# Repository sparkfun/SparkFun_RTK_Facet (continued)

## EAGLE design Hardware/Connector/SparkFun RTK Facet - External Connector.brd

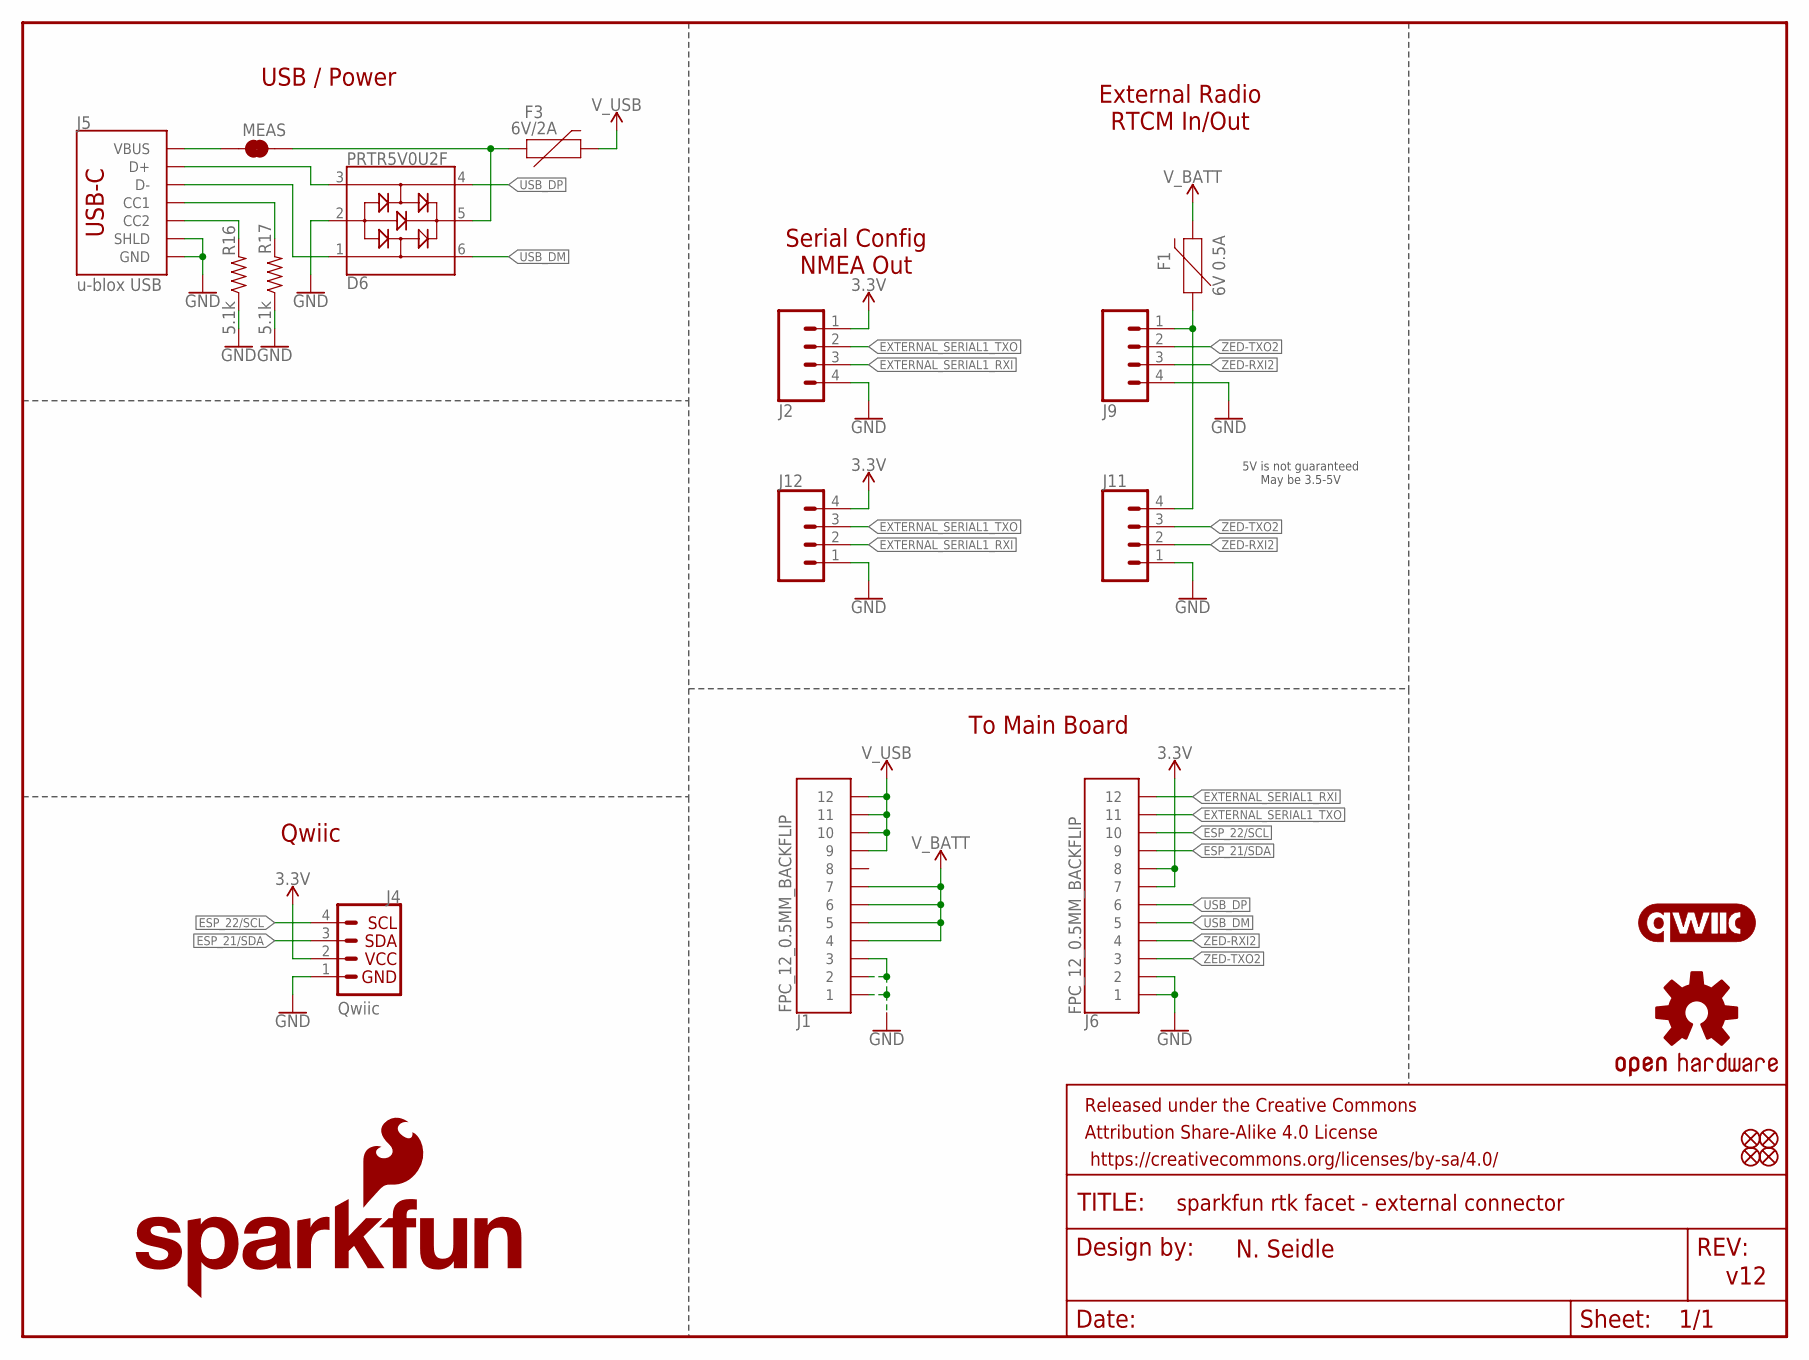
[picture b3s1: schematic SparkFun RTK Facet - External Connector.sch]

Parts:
D6: PRTR5V0U2F; SOT886
F1: 6V 0.5A; 0805
F3: 6V/2A; 1210
FRAME1: FRAME-LETTER; CREATIVE_COMMONS
J1, J6: FPC_12_0.5MM_BACKFLIP; FPC_12_DOUBLESIDED_BACKFLIP
J2, J9: CONN_04JST-SMD-LOCKING; JST-4-SMD-1.25MM-LOCKING
J4: Qwiic; JST04_1MM_RA
J5: u-blox USB; USB-C-16P-2LAYER-PADS
J11, J12: CONN_041X04_NO_SILK_NO_POP; 1X04_NO_SILK
JP21, JP61, JP71, JP81: FIDUCIALUFIDUCIAL; FIDUCIAL-MICRO
LOGO1: OSHW-LOGOMINI; OSHW-LOGO-MINI
LOGO2: SFE_LOGO_NAME_FLAME.1_INCH; SFE_LOGO_NAME_FLAME_.1
LOGO3: QWIIC_LOGO_CONNECTOR; QWIIC_5.5MM
MEAS: JUMPER-COMBO_2_NC_TRACE; COMBO-JUMPER_2_NC_TRACE
R16, R17: 5.1k; 0603

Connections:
3.3V: J2.1, J4.2, J6.7, J6.8, J12.4
CC1: J5.A5 (CC1), R17.2
CC2: J5.B5 (CC2), R16.2
ESP_21/SDA: J4.3, J6.9
ESP_22/SCL: J4.4, J6.10
EXTERNAL_SERIAL1_RXI: J2.3, J6.12, J12.2
EXTERNAL_SERIAL1_TXO: J2.2, J6.11, J12.3
GND: D6.2, J1.1, J1.2, J1.3, J2.4, J4.1, J5.GND, J5.GND2 (GND), J5.SHLD1 (SHLD), J5.SHLD2 (SHLD), J5.SHLD3 (SHLD), J5.SHLD4 (SHLD), J6.1, J6.2, J9.4, J11.1, J12.1, R16.1, R17.1
unnamed: F1.1, J9.1, J11.4
USB1_D_M: D6.1, J5.A7 (D-), J5.B7 (D-)
USB1_D_P: D6.3, J5.A6 (D+), J5.B6 (D+)
USB_DM: D6.6, J6.5
USB_DP: D6.4, J6.6
VIN: J5.VBUS1 (VBUS), J5.VBUS2 (VBUS), MEAS.1, MEAS.3 (1)
VIN1: D6.5, F3.1, MEAS.2, MEAS.4 (2)
V_BATT: F1.2, J1.4, J1.5, J1.6, J1.7
V_USB: F3.2, J1.9, J1.10, J1.11, J1.12
ZED-RXI2: J6.4, J9.3, J11.2
ZED-TXO2: J6.3, J9.2, J11.3

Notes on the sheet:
v12
USB / Power
External Radio RTCM In/Out
Serial Config NMEA Out
5V is not guaranteed May be 3.5-5V
To Main Board
Qwiic
N. Seidle

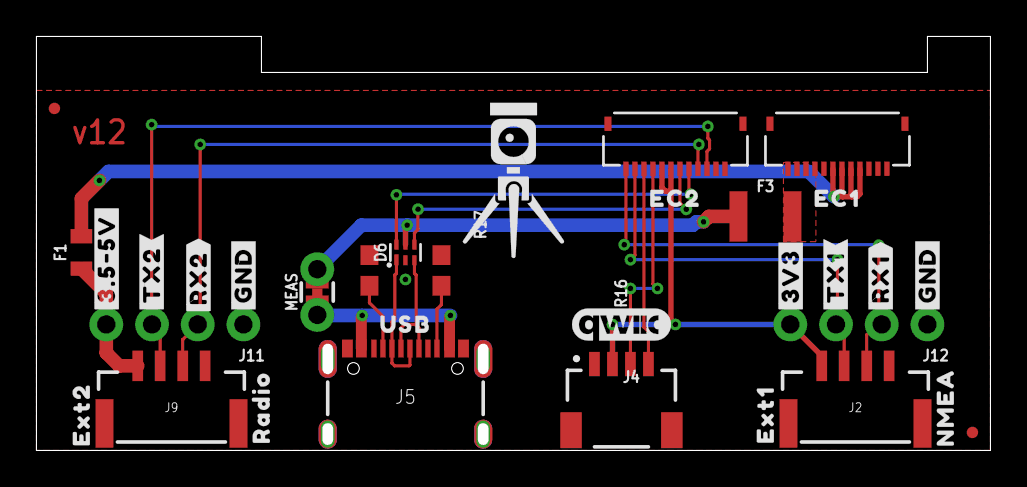
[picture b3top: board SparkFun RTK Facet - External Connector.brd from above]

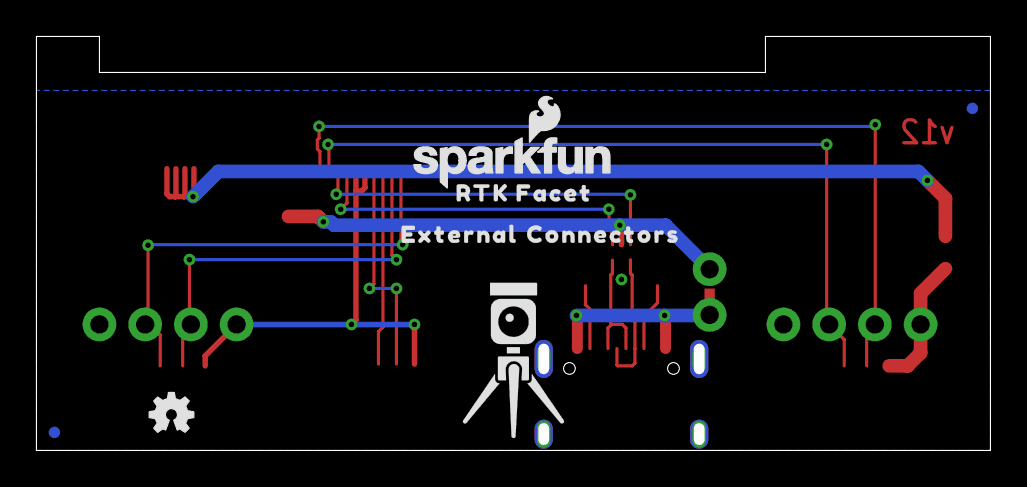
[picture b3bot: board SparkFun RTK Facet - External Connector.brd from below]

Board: 2 copper layers, 53.0 x 23.0 mm, 42 parts (8 on the bottom side), 19 nets.

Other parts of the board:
U$1: USB0
U$2: CONNECTORS1
U$3, U$13: RTK5#SVG0
U$4: EXT10
U$5: #3V3#0
U$6: EXT22
U$7: NMEA1
U$8: EC10
U$9: EXTERNAL0
U$11: EC21
U$12: RADIO3
U$14: RTK_FACET0
U$23: #3#5#5V#0
U$38, U$82: #GND#0
U$39: #RX2#2
U$40: #TX2#1
U$65: #TX1#1
U$68: #RX1#2

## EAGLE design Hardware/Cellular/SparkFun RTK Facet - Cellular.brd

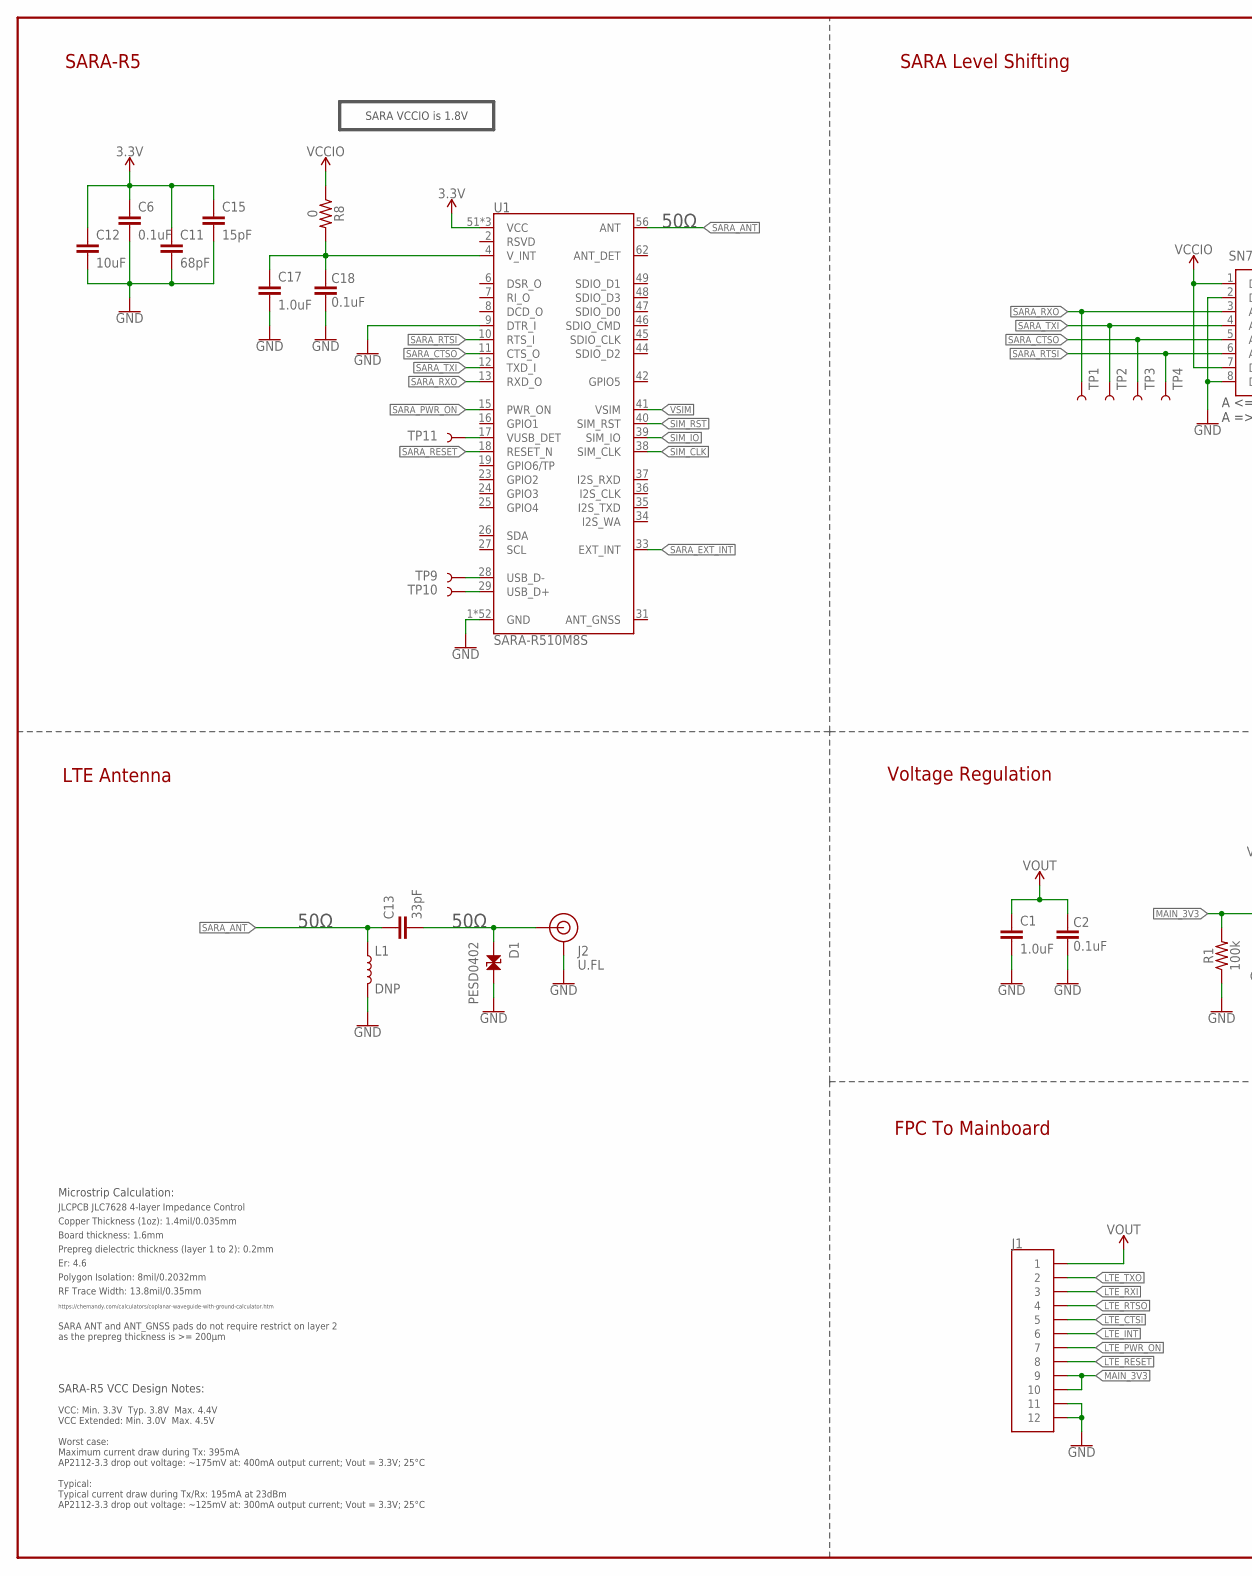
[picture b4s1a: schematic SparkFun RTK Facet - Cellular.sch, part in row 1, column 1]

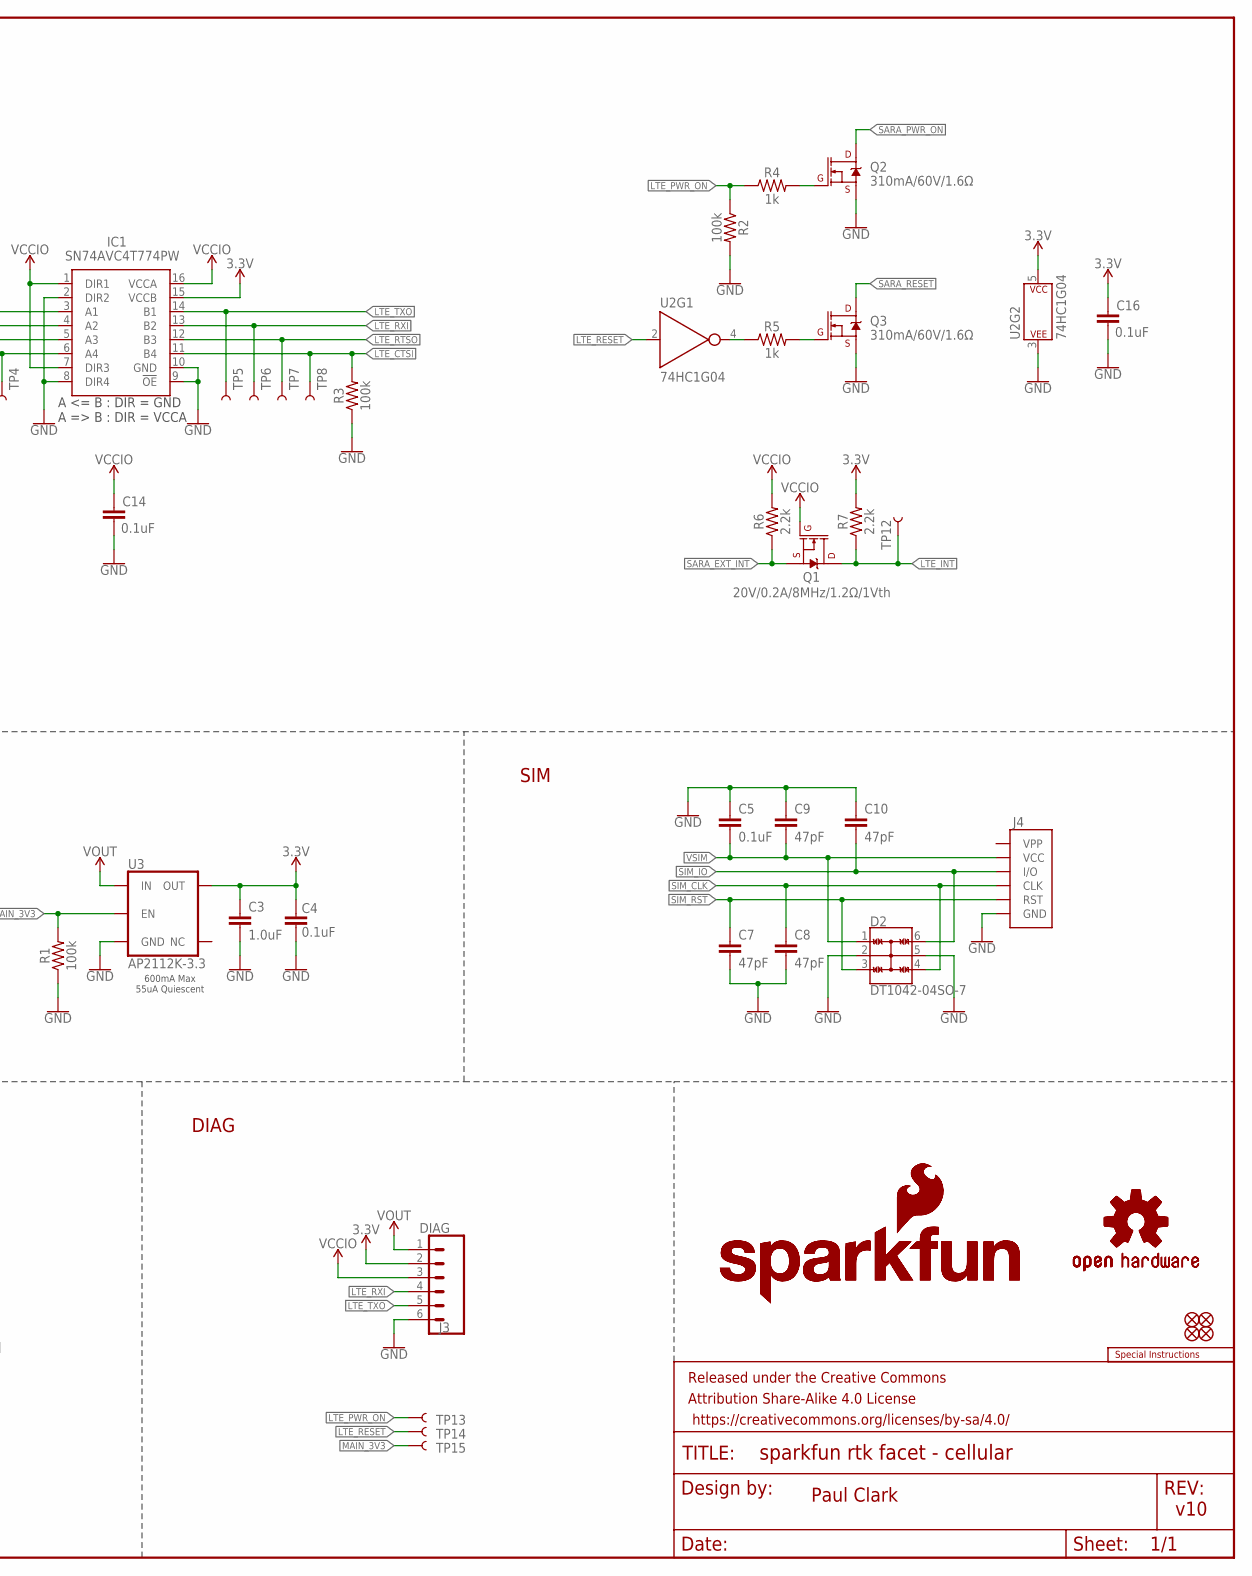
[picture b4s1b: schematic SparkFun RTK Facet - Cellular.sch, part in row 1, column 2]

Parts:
C1, C3, C17: 1.0uF; 0603
C2, C4, C5, C6, C14, C16, C18: 0.1uF; 0603
C7, C8, C9, C10: 47pF; 0603
C11: 68pF; 0603
C12: 10uF; 0603
C13: 33pF; 0402
C15: 15pF; 0603
D1: PESD0402; 0402
D2: DT1042-04SO-7; SOT23-6L
FID1, FID2, FID3, FID4: FIDUCIAL1X2; FIDUCIAL-1X2
FRAME3: FRAME-LEDGER; CREATIVE_COMMONS
IC1: SN74AVC4T774PW; SOP65P640X120-16N
J1: FPC_12_0.5MM_BACKFLIP; FPC_12_DOUBLESIDED_BACKFLIP
J2: U.FL
J3: DIAG; 1X06_NO_SILK
J4: SIMHOLDER-PUSHPUSH-REDUCED-PADS; NANO_SIM_PP_REDUCED_PADS
L1: DNP; 0402_COILCRAFT
LOGO1: SPECIAL_INSTRUCTIONS-ORDERING; ORDERING_INSTRUCTIONS
LOGO2, LOGO5: SFE_LOGO_NAME_FLAME.1_INCH; SFE_LOGO_NAME_FLAME_.1
LOGO3, LOGO4: OSHW-LOGOMINI; OSHW-LOGO-MINI
Q1: 20V/0.2A/8MHz/1.2Ω/1Vth; SOT-416FL
Q2, Q3: 310mA/60V/1.6Ω; SOT323
R1, R2, R3: 100k; 0603
R4, R5: 1k; 0603
R6, R7: 2.2k; 0603
R8: 0; 0603
TP1, TP2, TP3, TP4, TP5, TP6, TP7, TP8, TP9, TP10, TP11, TP12, TP13, TP14, TP15: TEST-POINT3; PAD.03X.03
U1: SARA-R510M8S; SARA-LGA
U2: 74HC1G04; SOT353
U3: AP2112K-3.3; SOT23-5

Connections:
3.3V: C3.1, C4.2, C6.1, C11.1, C12.1, C15.1, C16.1, IC1.15 (VCCB), J3.2, R7.2, U1.51 (VCC), U1.52 (VCC), U1.53 (VCC), U2.5 (P$V+), U3.5 (OUT)
GND: C1.2, C2.1, C3.2, C4.1, C5.1, C6.2, C7.2, C8.2, C9.1, C10.1, C11.2, C12.2, C14.2, C15.2, C16.2, C17.2, C18.1, D1.2, D2.2, D2.5, IC1.2 (DIR2), IC1.8 (DIR4), IC1.9 (!OE), IC1.10 (GND), J1.11, J1.12, J2.1 (GND), J2.2 (GND), J3.6, J4.C5 (GND), L1.P$2 (2), Q2.2 (S), Q3.2 (S), R1.1, R2.2, R3.1, U1.1 (GND), U1.3 (GND), U1.5 (GND), U1.9 (DTR_I), U1.14 (GND), U1.20 (GND), U1.21 (GND), U1.22 (GND), U1.30 (GND), U1.32 (GND), U1.43 (GND), U1.50 (GND), U1.54 (GND), U1.55 (GND), U1.57 (GND), U1.58 (GND), U1.59 (GND), U1.60 (GND), U1.61 (GND), U1.63 (GND), U1.64 (GND), U1.65 (GND), U1.66 (GND), U1.67 (GND), U1.68 (GND), U1.69 (GND), U1.70 (GND), U1.71 (GND), U1.72 (GND), U1.73 (GND), U1.74 (GND), U1.75 (GND), U1.76 (GND), U1.77 (GND), U1.78 (GND), U1.79 (GND), U1.80 (GND), U1.81 (GND), U1.82 (GND), U1.83 (GND), U1.84 (GND), U1.85 (GND), U1.86 (GND), U1.87 (GND), U1.88 (GND), U1.89 (GND), U1.90 (GND), U1.91 (GND), U1.92 (GND), U1.93 (GND), U1.94 (GND), U1.95 (GND), U1.96 (GND), U2.3 (P$V-), U3.2 (GND)
LTE_!RESET!: J1.8, TP14.1, U2.2 (A)
LTE_CTSI: IC1.11 (B4), J1.5, R3.2, TP8.1
LTE_INT: J1.6, Q1.3 (D), R7.1, TP12.1
LTE_PWR_ON: J1.7, R2.1, R4.1, TP13.1
LTE_RTSO: IC1.12 (B3), J1.4, TP7.1
LTE_RXI: IC1.13 (B2), J1.3, J3.4, TP6.1
LTE_TXO: IC1.14 (B1), J1.2, J3.5, TP5.1
MAIN_3V3: J1.9, J1.10, R1.2, TP15.1, U3.3 (EN)
unnamed: TP9.1, U1.28 (USB_D-)
unnamed: TP10.1, U1.29 (USB_D+)
unnamed: TP11.1, U1.17 (VUSB_DET)
unnamed: C13.2, D1.1, J2.FEED (SIGNAL)
unnamed: Q2.1 (G), R4.2
unnamed: Q3.1 (G), R5.2
unnamed: R5.1, U2.4 (Y)
unnamed: C17.1, C18.2, R8.2, U1.4 (V_INT)
SARA_!RESET!: Q3.3 (D), U1.18 (RESET_N)
SARA_ANT: C13.1, L1.P$1 (1), U1.56 (ANT)
SARA_CTSO: IC1.5 (A3), TP3.1, U1.11 (CTS_O)
SARA_EXT_INT: Q1.2 (S), R6.1, U1.33 (EXT_INT)
SARA_PWR_ON: Q2.3 (D), U1.15 (PWR_ON)
SARA_RTSI: IC1.6 (A4), TP4.1, U1.10 (RTS_I)
SARA_RXO: IC1.3 (A1), TP1.1, U1.13 (RXD_O)
SARA_TXI: IC1.4 (A2), TP2.1, U1.12 (TXD_I)
SIM_CLK: C8.1, D2.4, J4.C3 (CLK), U1.38 (SIM_CLK)
SIM_IO: C10.2, D2.6, J4.C7 (I/O), U1.39 (SIM_IO)
SIM_RST: C7.1, D2.3, J4.C2 (RST), U1.40 (SIM_RST)
VCCIO: C14.1, IC1.1 (DIR1), IC1.7 (DIR3), IC1.16 (VCCA), J3.3, Q1.1 (G), R6.2, R8.1
VOUT: C1.1, C2.2, J1.1, J3.1, U3.1 (IN)
VSIM: C5.2, C9.2, D2.1, J4.C1 (VCC), U1.41 (VSIM)

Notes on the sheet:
v10
FPC To Mainboard
SARA-R5
50Ω
SARA VCCIO is 1.8V
SIM
DIAG
LTE Antenna
Board thickness: 1.6mm
Er: 4.6
Copper Thickness (1oz): 1.4mil/0.035mm
RF Trace Width: 13.8mil/0.35mm
Polygon Isolation: 8mil/0.2032mm
Prepreg dielectric thickness (layer 1 to 2): 0.2mm
https://chemandy.com/calculators/coplanar-waveguide-with-ground-calculator.htm
Microstrip Calculation:
SARA ANT and ANT_GNSS pads do not require restrict on layer 2 as the prepreg thickness is >= 200µm
SARA Level Shifting
SARA-R5 VCC Design Notes:
VCC: Min. 3.3V Typ. 3.8V Max. 4.4V VCC Extended: Min. 3.0V Max. 4.5V Worst case: Maximum current draw during Tx: 395mA AP2112-3.3 drop out voltage: ~175mV at: 400mA output current; Vout = 3.3V; 25°C Typical: Typical current draw during Tx/Rx: 195mA at 23dBm AP2112-3.3 drop out voltage: ~125mV at: 3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
Voltage Regulation
600mA Max 55uA Quiescent
JLCPCB JLC7628 4-layer Impedance Control
Paul Clark

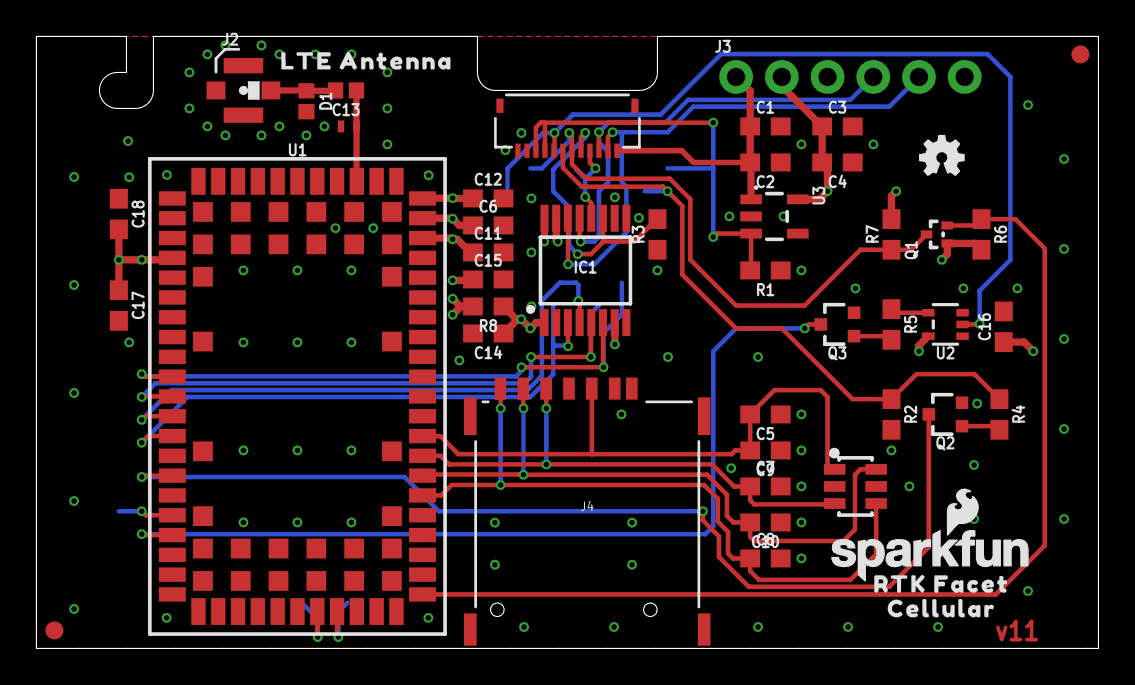
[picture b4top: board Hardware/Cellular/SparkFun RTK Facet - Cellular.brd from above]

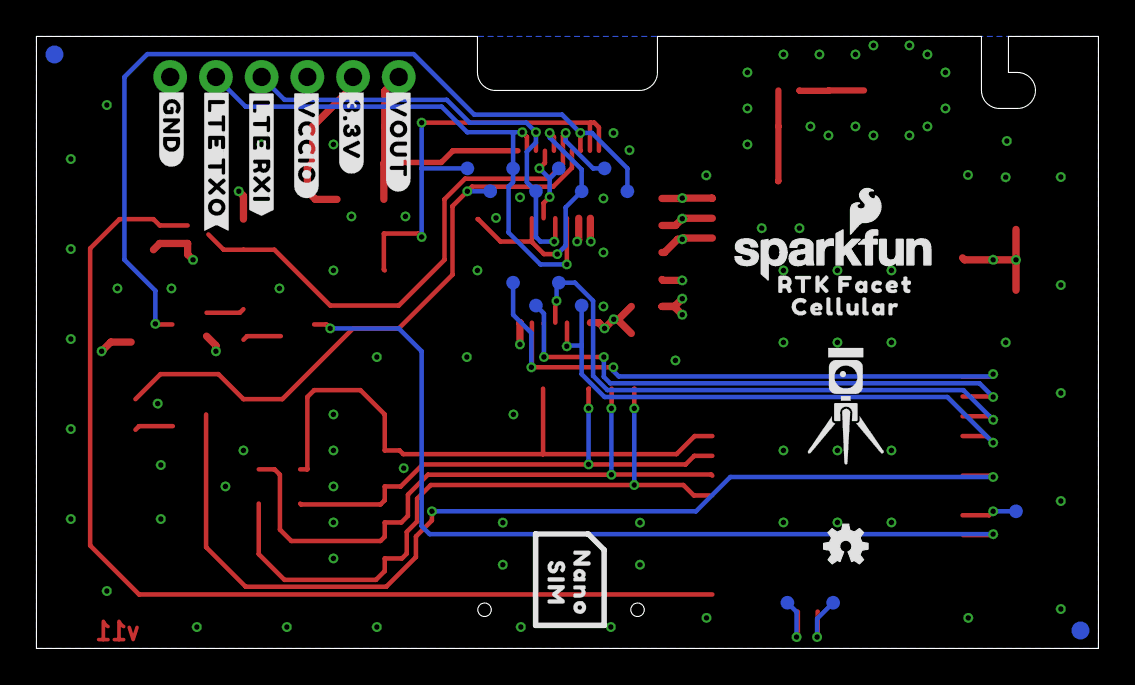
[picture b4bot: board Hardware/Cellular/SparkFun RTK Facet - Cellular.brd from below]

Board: 4 copper layers, 59.0 x 34.0 mm, 79 parts (30 on the bottom side), 32 nets.

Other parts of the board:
U$1, U$14: RTK_FACET0
U$2, U$3: CELLULAR1
U$4: #VOUT#0
U$5: #3#3V#0
U$6: #VCCIO#0
U$7: #LTE_RXI#0
U$8: #LTE_TXO#0
U$9: #GND#0
U$10: LTE_ANTENNA0
U$15: RTK5#SVG0
U$130: NANO0
U$131: SIM0

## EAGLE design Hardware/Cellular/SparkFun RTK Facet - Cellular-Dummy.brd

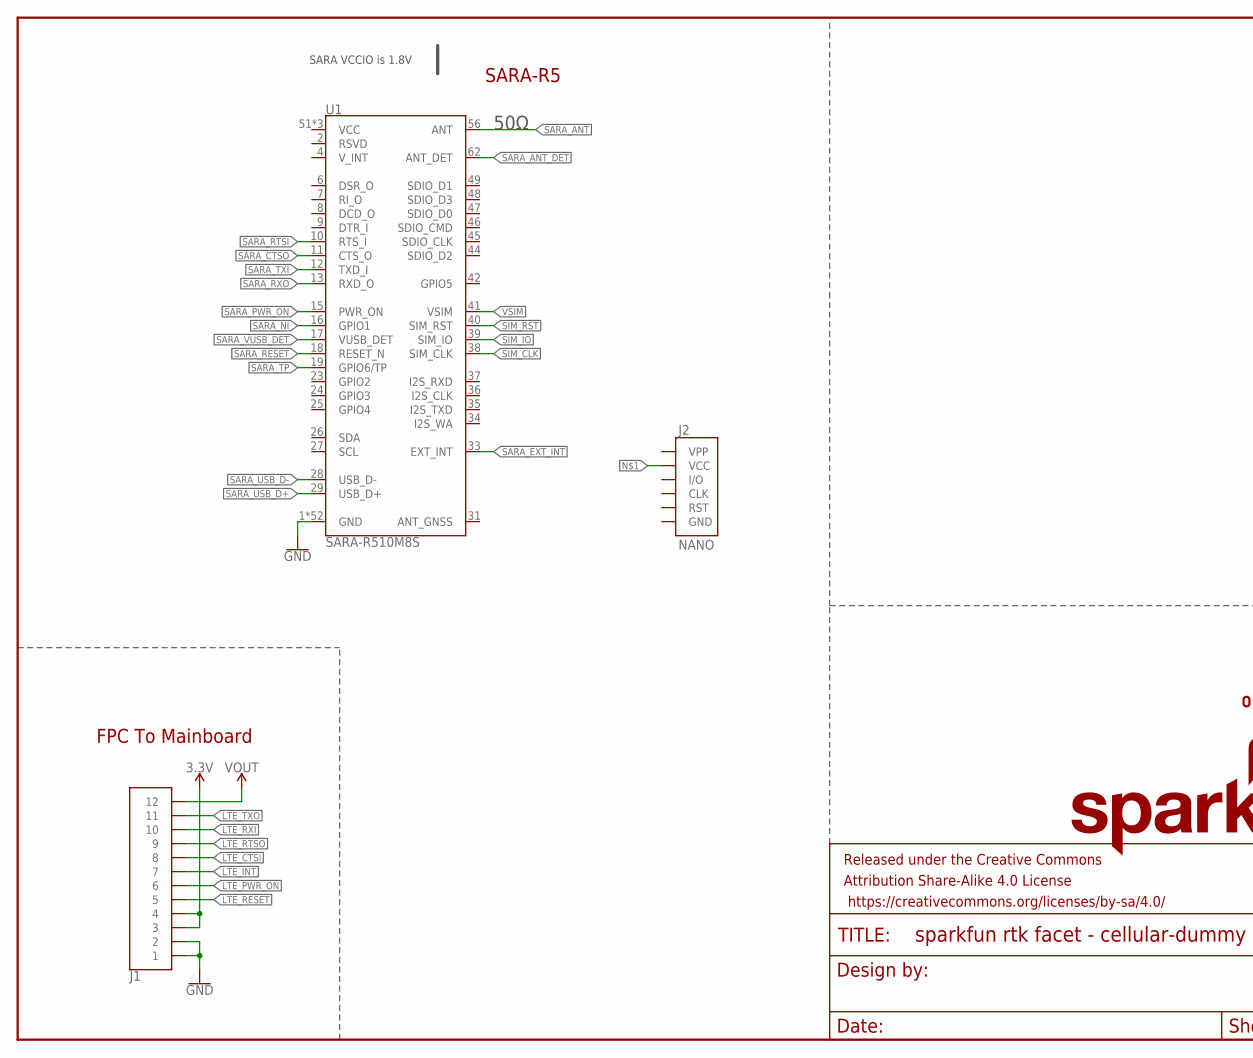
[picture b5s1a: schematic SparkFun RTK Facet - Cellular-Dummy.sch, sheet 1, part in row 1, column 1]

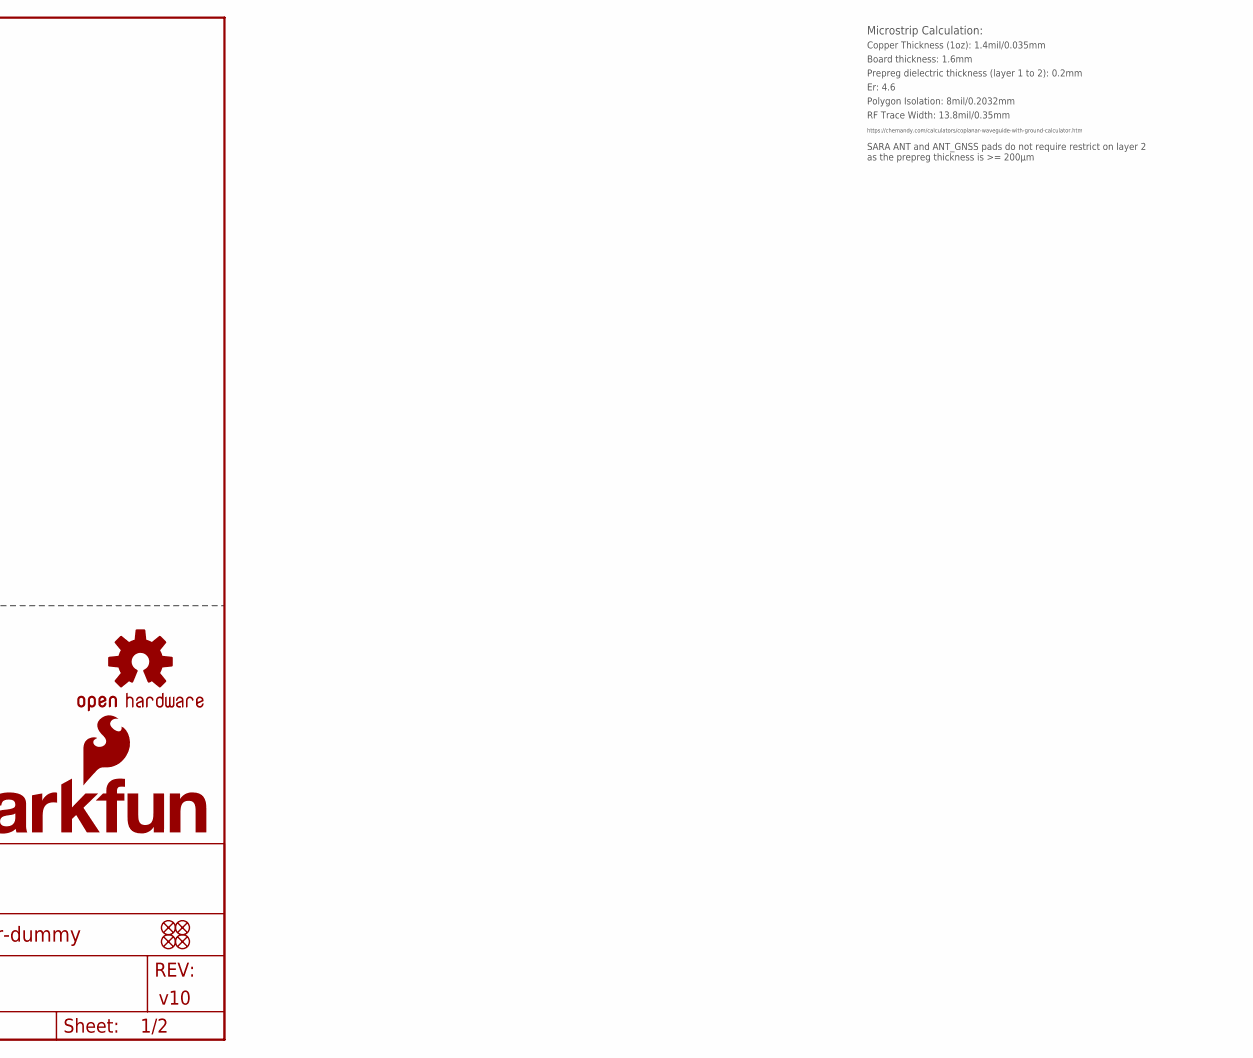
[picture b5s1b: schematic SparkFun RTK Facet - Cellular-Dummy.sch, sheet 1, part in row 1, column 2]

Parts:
FID1, FID2, FID3, FID4: FIDUCIAL1X2; FIDUCIAL-1X2
FRAME1: FRAME-LETTER; CREATIVE_COMMONS
J1: FPC_12_0.5MM_BACKFLIP; FPC_12_DOUBLESIDED_BACKFLIP
J2: NANO; NANO_SIM_PP
LOGO3: OSHW-LOGOMINI; OSHW-LOGO-MINI
LOGO5: SFE_LOGO_NAME_FLAME.1_INCH; SFE_LOGO_NAME_FLAME_.1
U1: SARA-R510M8S; SARA-LGA

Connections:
3.3V: J1.3, J1.4
GND: J1.1, J1.2, J2.C5 (GND), U1.1 (GND), U1.3 (GND), U1.5 (GND), U1.14 (GND), U1.20 (GND), U1.21 (GND), U1.22 (GND), U1.30 (GND), U1.32 (GND), U1.43 (GND), U1.50 (GND), U1.54 (GND), U1.55 (GND), U1.57 (GND), U1.58 (GND), U1.59 (GND), U1.60 (GND), U1.61 (GND), U1.63 (GND), U1.64 (GND), U1.65 (GND), U1.66 (GND), U1.67 (GND), U1.68 (GND), U1.69 (GND), U1.70 (GND), U1.71 (GND), U1.72 (GND), U1.73 (GND), U1.74 (GND), U1.75 (GND), U1.76 (GND), U1.77 (GND), U1.78 (GND), U1.79 (GND), U1.80 (GND), U1.81 (GND), U1.82 (GND), U1.83 (GND), U1.84 (GND), U1.85 (GND), U1.86 (GND), U1.87 (GND), U1.88 (GND), U1.89 (GND), U1.90 (GND), U1.91 (GND), U1.92 (GND), U1.93 (GND), U1.94 (GND), U1.95 (GND), U1.96 (GND)
LTE_!RESET!: J1.5
LTE_CTSI: J1.8
LTE_INT: J1.7
LTE_PWR_ON: J1.6
LTE_RTSO: J1.9
LTE_RXI: J1.10
LTE_TXO: J1.11
SARA_!RESET!: U1.18 (RESET_N)
SARA_ANT: U1.56 (ANT)
SARA_ANT_DET: U1.62 (ANT_DET)
SARA_CTSO: U1.11 (CTS_O)
SARA_EXT_INT: U1.33 (EXT_INT)
SARA_NI: U1.16 (GPIO1)
SARA_PWR_ON: U1.15 (PWR_ON)
SARA_RTSI: U1.10 (RTS_I)
SARA_RXO: U1.13 (RXD_O)
SARA_TP: U1.19 (GPIO6/TP)
SARA_TXI: U1.12 (TXD_I)
SARA_USB_D+: U1.29 (USB_D+)
SARA_USB_D-: U1.28 (USB_D-)
SARA_VUSB_DET: U1.17 (VUSB_DET)
SIM_CLK: U1.38 (SIM_CLK)
SIM_IO: U1.39 (SIM_IO)
SIM_RST: U1.40 (SIM_RST)
VCC: U1.51 (VCC), U1.52 (VCC), U1.53 (VCC)
VOUT: J1.12
VSIM: U1.41 (VSIM)

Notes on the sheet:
v10
FPC To Mainboard
SARA-R5
50Ω
SARA VCCIO is 1.8V
Board thickness: 1.6mm
Er: 4.6
Copper Thickness (1oz): 1.4mil/0.035mm
RF Trace Width: 13.8mil/0.35mm
Polygon Isolation: 8mil/0.2032mm
Prepreg dielectric thickness (layer 1 to 2): 0.2mm
https://chemandy.com/calculators/coplanar-waveguide-with-ground-calculator.htm
Microstrip Calculation:
SARA ANT and ANT_GNSS pads do not require restrict on layer 2 as the prepreg thickness is >= 200µm

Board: 2 copper layers, 15 parts (9 on the bottom side), 3 nets, no tracks yet.

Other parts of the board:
U$2: CELLULAR1
U$13: CELLULAR0
U$14: RTK_FACET0
U$130: NANO0
U$131: SIM0

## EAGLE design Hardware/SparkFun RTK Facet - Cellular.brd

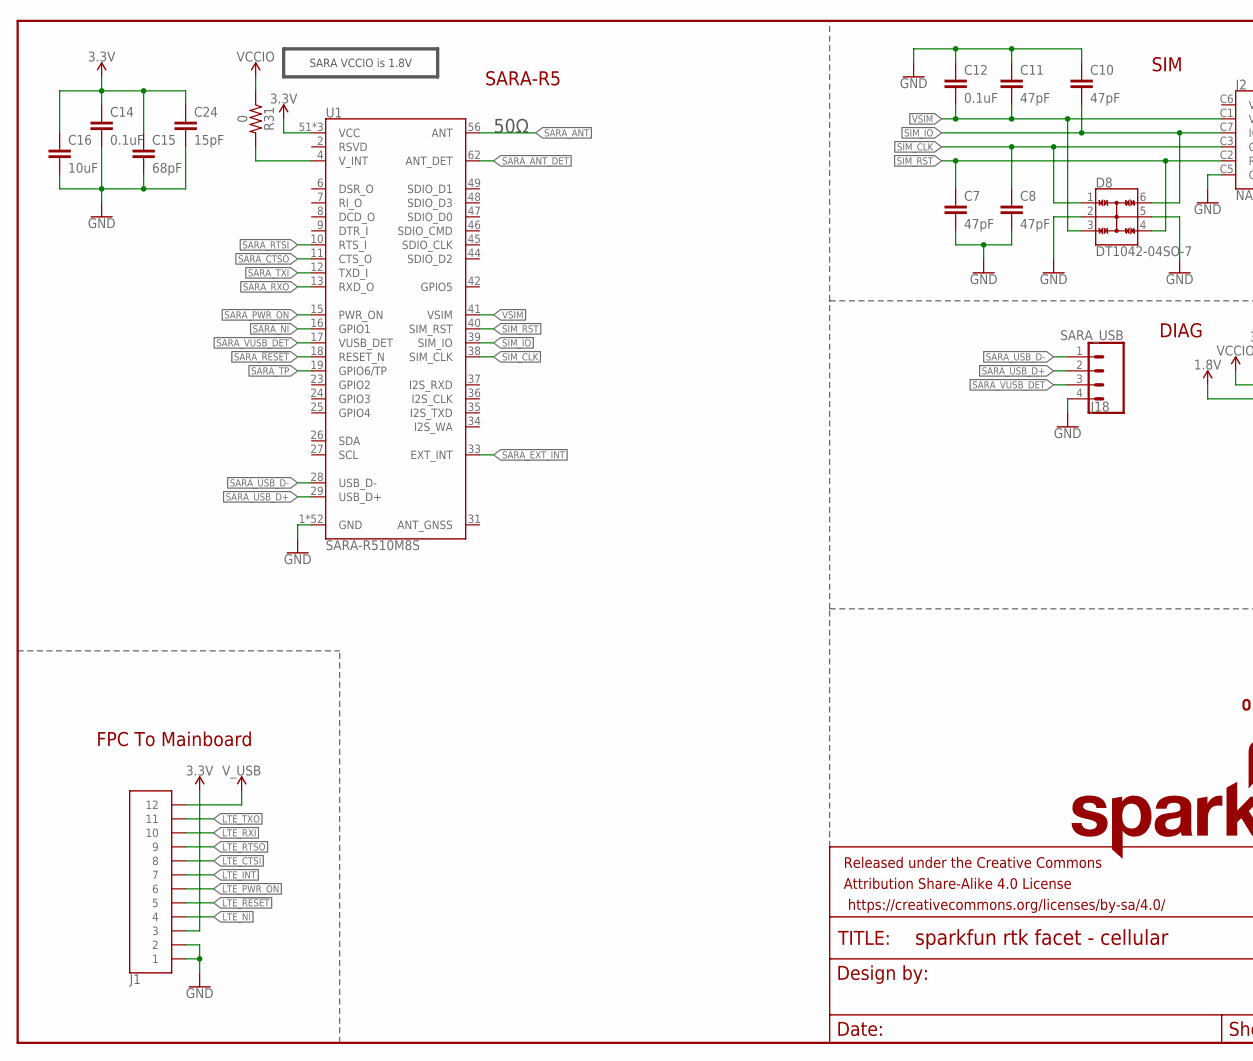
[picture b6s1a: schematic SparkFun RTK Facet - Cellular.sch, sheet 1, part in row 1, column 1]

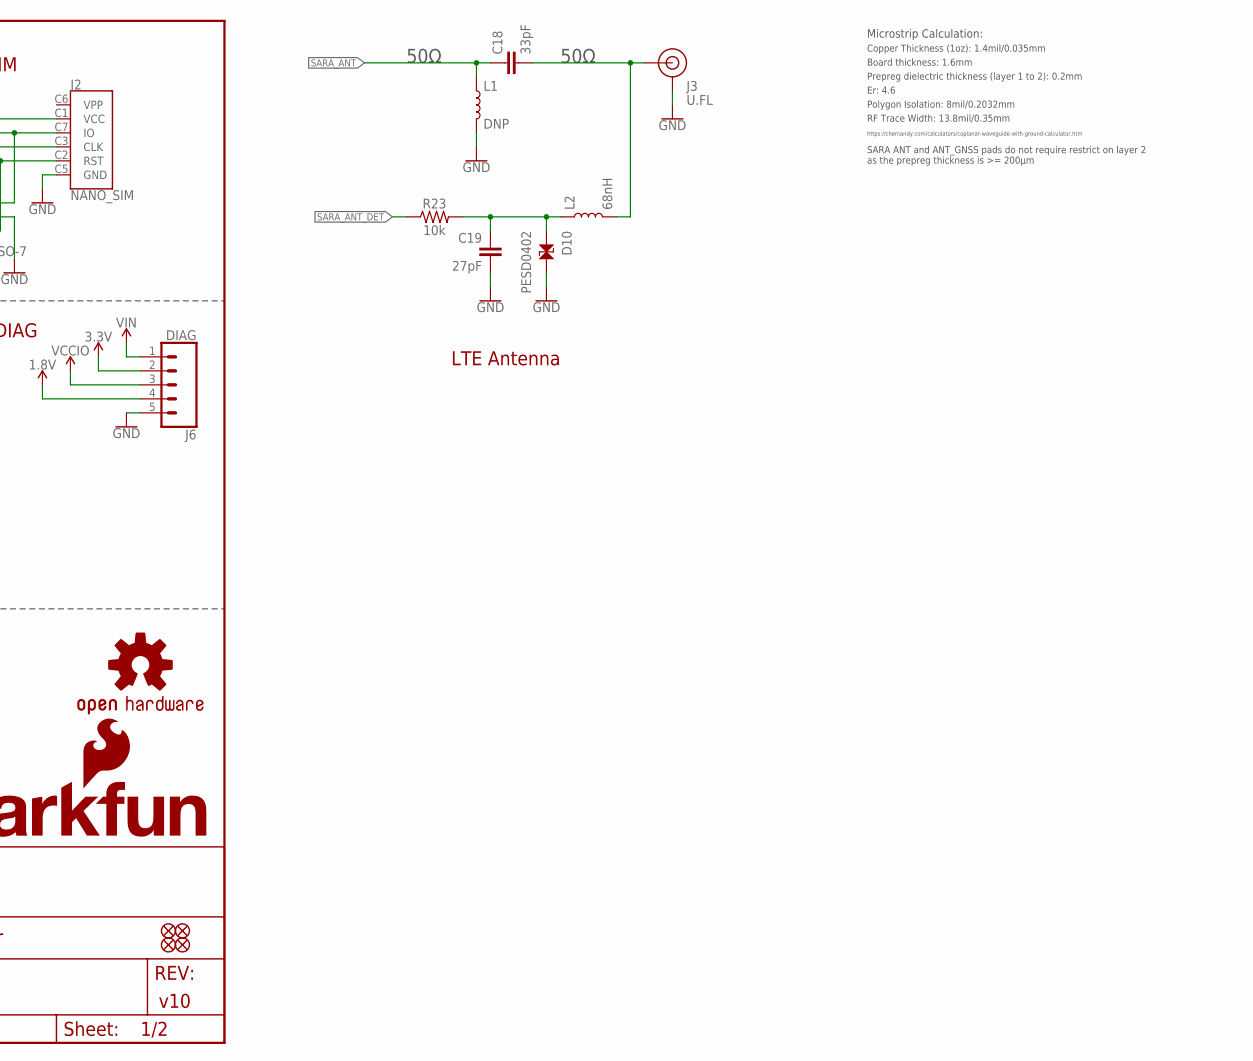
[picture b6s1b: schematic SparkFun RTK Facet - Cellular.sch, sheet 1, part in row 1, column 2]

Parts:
C7, C8, C10, C11: 47pF; 0603
C12, C14: 0.1uF; 0603
C15: 68pF; 0603
C16: 10uF; 0603
C18: 33pF; 0402
C19: 27pF; 0402
C24: 15pF; 0603
D8: DT1042-04SO-7; SOT23-6L
D10: PESD0402; 0402
FID1, FID2, FID3, FID4: FIDUCIAL1X2; FIDUCIAL-1X2
FRAME1: FRAME-LETTER; CREATIVE_COMMONS
J1: FPC_12_0.5MM_BACKFLIP; FPC_12_DOUBLESIDED_BACKFLIP
J2: NANO_SIM; NANO_SIM_WURTH_693043020611
J3: U.FL
J6: DIAG; 1X05_NO_SILK
J18: SARA_USB; 1X04_NO_SILK
L1: DNP; 0402_COILCRAFT
L2: 68nH; 0402_COILCRAFT
LOGO3: OSHW-LOGOMINI; OSHW-LOGO-MINI
LOGO5: SFE_LOGO_NAME_FLAME.1_INCH; SFE_LOGO_NAME_FLAME_.1
R23: 10k; 0603
R31: 0; 0603
U1: SARA-R510M8S; SARA-LGA

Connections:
1.8V: J6.4
3.3V: C14.1, C15.1, C16.1, C24.1, J1.3, J6.2, U1.51 (VCC), U1.52 (VCC), U1.53 (VCC); also elsewhere on the board
GND: C7.2, C8.2, C10.1, C11.1, C12.1, C14.2, C15.2, C16.2, C19.2, C24.2, D8.2, D8.5, D10.2, J1.1, J1.2, J2.C5 (GND), J3.1 (GND), J3.2 (GND), J6.5, J18.4, L1.P$2 (2), U1.1 (GND), U1.3 (GND), U1.5 (GND), U1.14 (GND), U1.20 (GND), U1.21 (GND), U1.22 (GND), U1.30 (GND), U1.32 (GND), U1.43 (GND), U1.50 (GND), U1.54 (GND), U1.55 (GND), U1.57 (GND), U1.58 (GND), U1.59 (GND), U1.60 (GND), U1.61 (GND), U1.63 (GND), U1.64 (GND), U1.65 (GND), U1.66 (GND), U1.67 (GND), U1.68 (GND), U1.69 (GND), U1.70 (GND), U1.71 (GND), U1.72 (GND), U1.73 (GND), U1.74 (GND), U1.75 (GND), U1.76 (GND), U1.77 (GND), U1.78 (GND), U1.79 (GND), U1.80 (GND), U1.81 (GND), U1.82 (GND), U1.83 (GND), U1.84 (GND), U1.85 (GND), U1.86 (GND), U1.87 (GND), U1.88 (GND), U1.89 (GND), U1.90 (GND), U1.91 (GND), U1.92 (GND), U1.93 (GND), U1.94 (GND), U1.95 (GND), U1.96 (GND); also elsewhere on the board
LTE_!RESET!: J1.5; also elsewhere on the board
LTE_CTSI: J1.8; also elsewhere on the board
LTE_INT: J1.7; also elsewhere on the board
LTE_NI: J1.4; also elsewhere on the board
LTE_PWR_ON: J1.6; also elsewhere on the board
LTE_RTSO: J1.9; also elsewhere on the board
LTE_RXI: J1.10; also elsewhere on the board
LTE_TXO: J1.11; also elsewhere on the board
unnamed: C18.2, J3.FEED (SIGNAL), L2.P$2 (2)
unnamed: C19.1, D10.1, L2.P$1 (1), R23.2
unnamed: R31.2, U1.4 (V_INT)
SARA_!RESET!: U1.18 (RESET_N); also elsewhere on the board
SARA_ANT: C18.1, L1.P$1 (1), U1.56 (ANT)
SARA_ANT_DET: R23.1, U1.62 (ANT_DET)
SARA_CTSO: U1.11 (CTS_O); also elsewhere on the board
SARA_EXT_INT: U1.33 (EXT_INT); also elsewhere on the board
SARA_NI: U1.16 (GPIO1); also elsewhere on the board
SARA_PWR_ON: U1.15 (PWR_ON); also elsewhere on the board
SARA_RTSI: U1.10 (RTS_I); also elsewhere on the board
SARA_RXO: U1.13 (RXD_O); also elsewhere on the board
SARA_TP: U1.19 (GPIO6/TP)
SARA_TXI: U1.12 (TXD_I); also elsewhere on the board
SARA_USB_D+: J18.2, U1.29 (USB_D+)
SARA_USB_D-: J18.1, U1.28 (USB_D-)
SARA_VUSB_DET: J18.3, U1.17 (VUSB_DET)
SIM_CLK: C8.1, D8.1, J2.C3 (CLK), U1.38 (SIM_CLK)
SIM_IO: C10.2, D8.6, J2.C7 (IO), U1.39 (SIM_IO)
SIM_RST: C7.1, D8.4, J2.C2 (RST), U1.40 (SIM_RST)
VCCIO: J6.3, R31.1; also elsewhere on the board
VIN: J6.1
VSIM: C11.2, C12.2, D8.3, J2.C1 (VCC), U1.41 (VSIM)
V_USB: J1.12

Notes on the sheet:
v10
FPC To Mainboard
SARA-R5
50Ω
SARA VCCIO is 1.8V
SIM
DIAG
LTE Antenna
Board thickness: 1.6mm
Er: 4.6
Copper Thickness (1oz): 1.4mil/0.035mm
RF Trace Width: 13.8mil/0.35mm
Polygon Isolation: 8mil/0.2032mm
Prepreg dielectric thickness (layer 1 to 2): 0.2mm
https://chemandy.com/calculators/coplanar-waveguide-with-ground-calculator.htm
Microstrip Calculation:
SARA ANT and ANT_GNSS pads do not require restrict on layer 2 as the prepreg thickness is >= 200µm
